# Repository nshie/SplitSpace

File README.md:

# SplitSpace
A regular 60% keyboard with the spacebar split into three buttons

### Motivation
Thumbs are our most dextrous digits, so why would we ever limit them to one button (let alone one SHARED button) on a keyboard? Every other finger is assigned numerous keys... This keyboard is a crude attempt to remedy that. It doesn't fix a lot of other issues with keyboards, but those are separate projects.

(My old keyboard PCB broke and I needed a replacement)

### Design
- fits in KBDFans 5 degree 60% case (the case I owned at the time of designing this PCB)
- hotswappable with MX style switches
- USB Type-C
- RGB underglow
- 3 spacebar keys
  - 2.25u, 1.25, and 2.75u (shift and modifier keys in ANSI layout keycaps)

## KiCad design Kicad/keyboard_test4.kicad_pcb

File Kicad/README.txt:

keyboard_test6 is the final production file

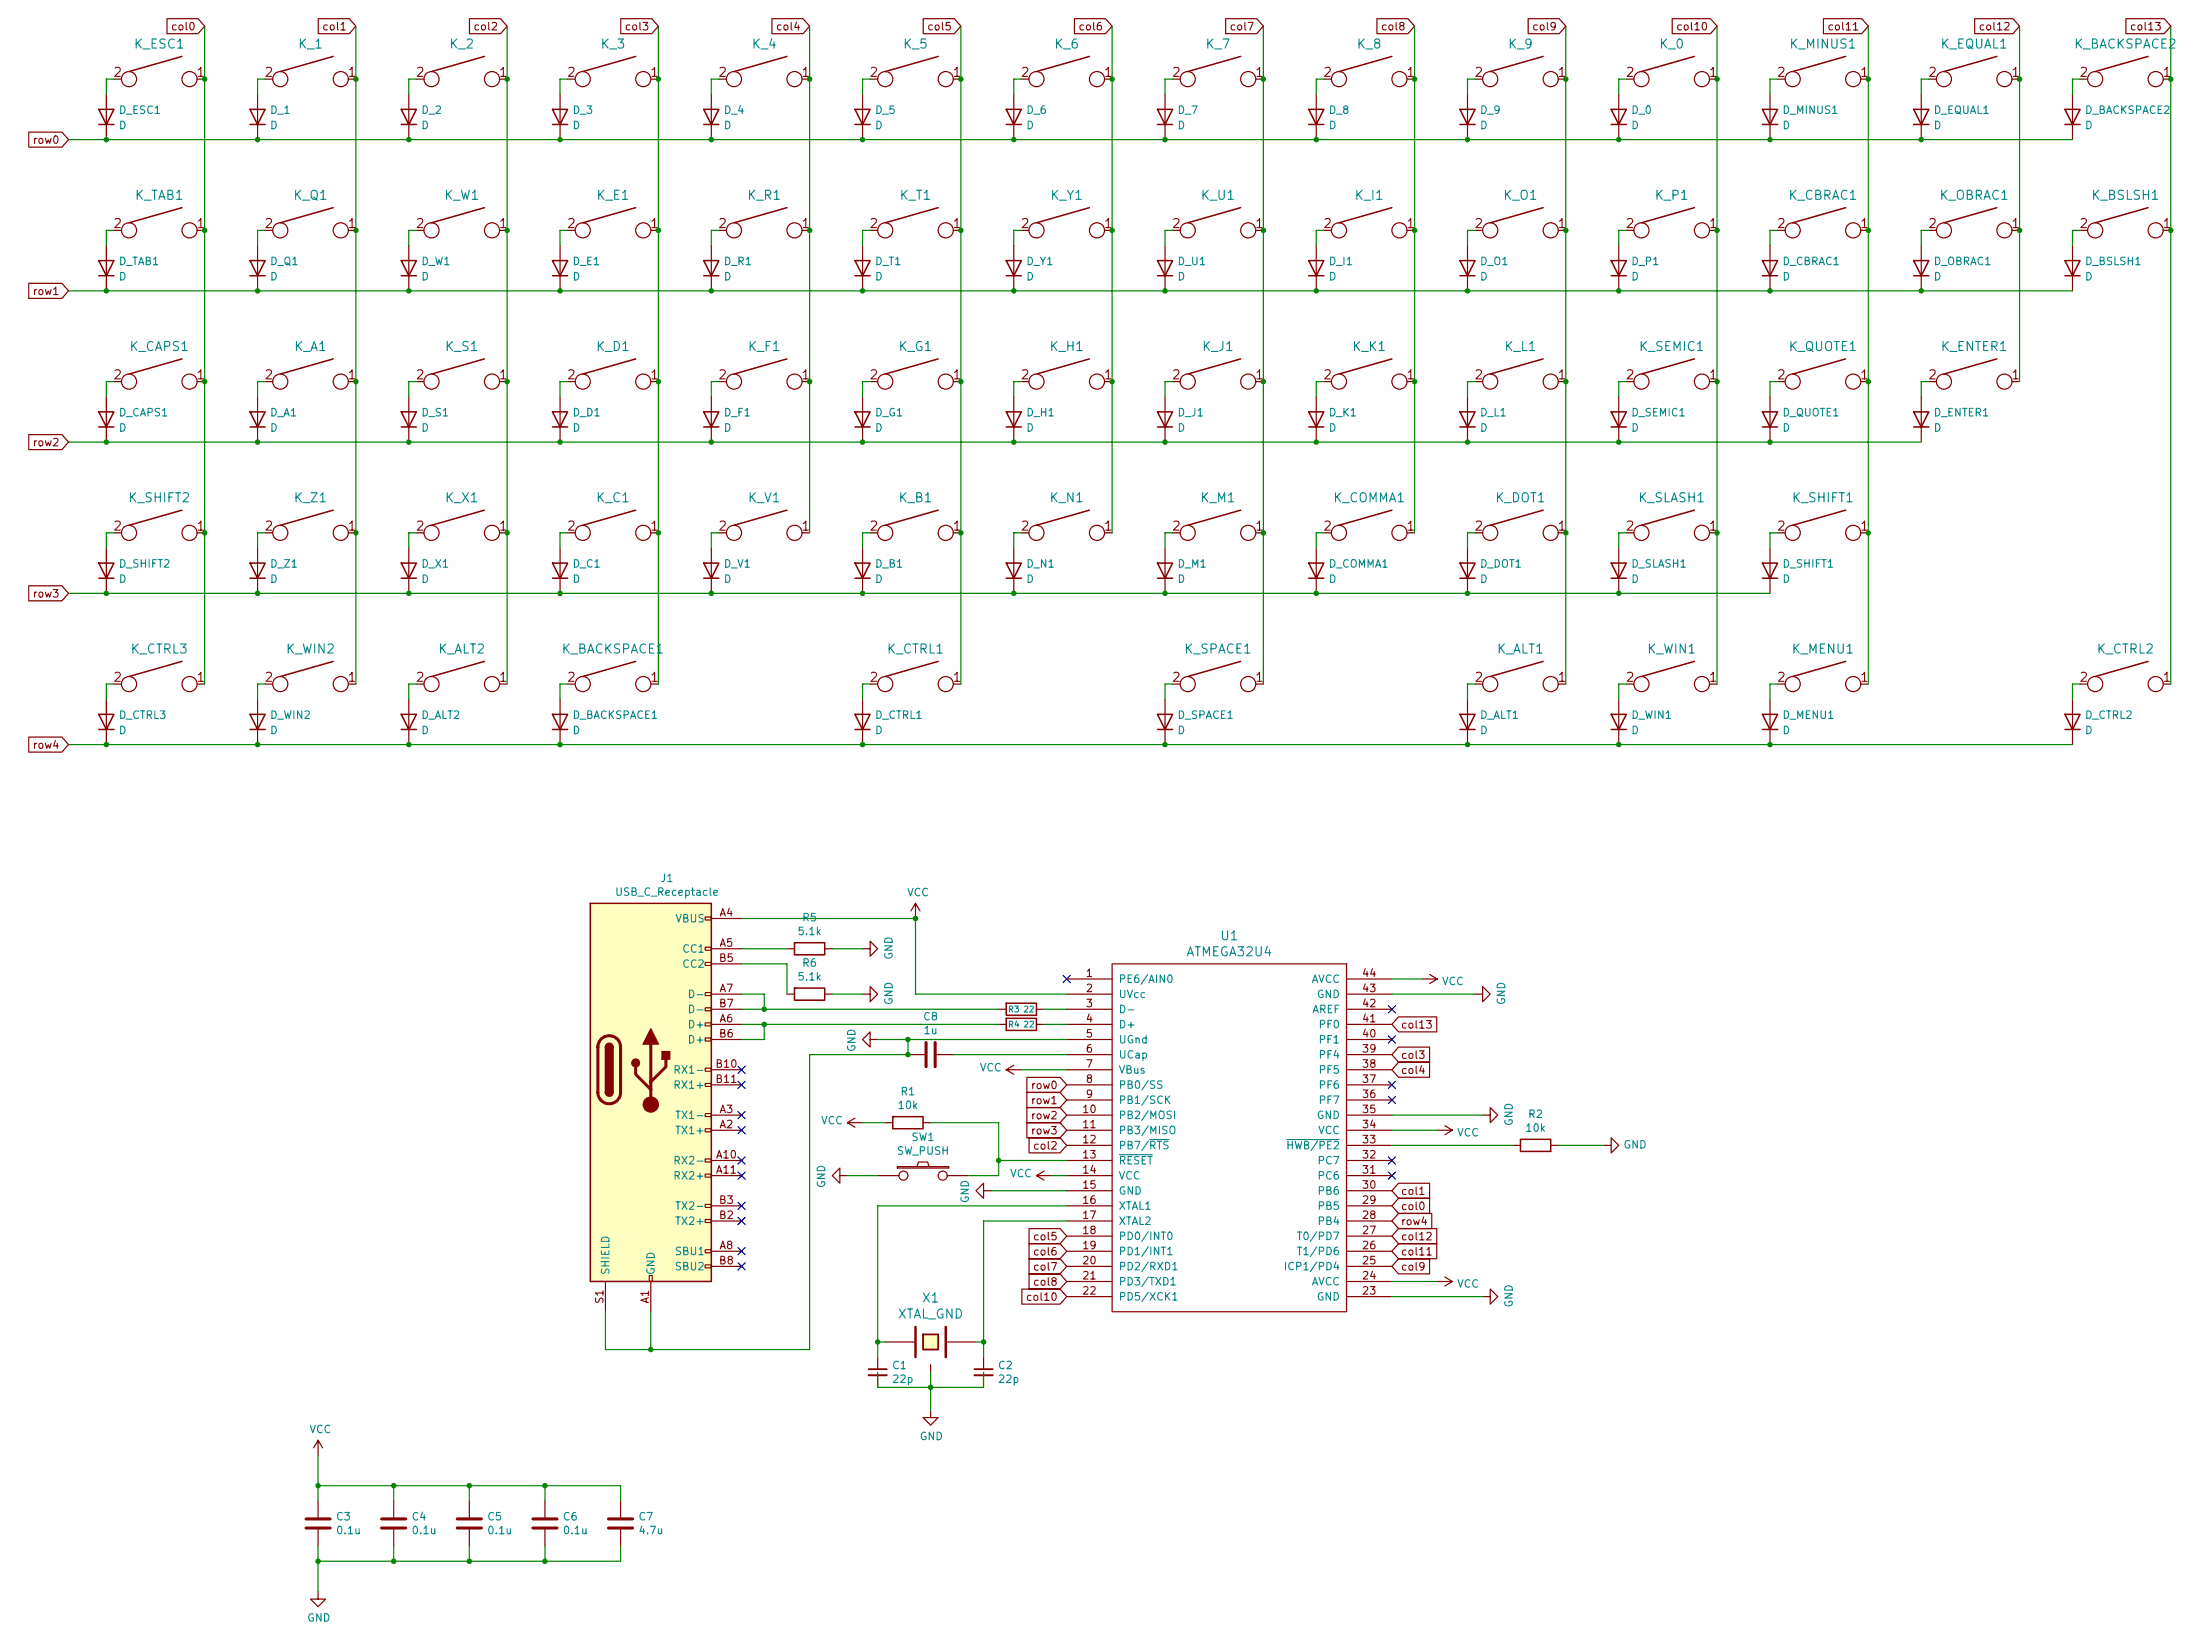
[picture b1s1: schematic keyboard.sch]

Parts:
C1, C2: 22p; C_0805_2012Metric_Pad1.15x1.40mm_HandSolder
C3, C4, C5, C6: 0.1u; C_0805_2012Metric_Pad1.15x1.40mm_HandSolder
C7: 4.7u; C_0805_2012Metric_Pad1.15x1.40mm_HandSolder
C8: 1u
D_0, D_1, D_2, D_3, D_4, D_5, D_6, D_7, D_8, D_9: D; D_SOD123_axial
D_A1: D; D_SOD123_axial
D_ALT1, D_ALT2: D; D_SOD123_axial
D_B1: D; D_SOD123_axial
D_BACKSPACE1, D_BACKSPACE2: D; D_SOD123_axial
D_BSLSH1: D; D_SOD123_axial
D_C1: D; D_SOD123_axial
D_CAPS1: D; D_SOD123_axial
D_CBRAC1: D; D_SOD123_axial
D_COMMA1: D; D_SOD123_axial
D_CTRL1, D_CTRL2, D_CTRL3: D; D_SOD123_axial
D_D1: D; D_SOD123_axial
D_DOT1: D; D_SOD123_axial
D_E1: D; D_SOD123_axial
D_ENTER1: D; D_SOD123_axial
D_EQUAL1: D; D_SOD123_axial
D_ESC1: D; D_SOD123_axial
D_F1: D; D_SOD123_axial
D_G1: D; D_SOD123_axial
D_H1: D; D_SOD123_axial
D_I1: D; D_SOD123_axial
D_J1: D; D_SOD123_axial
D_K1: D; D_SOD123_axial
D_L1: D; D_SOD123_axial
D_M1: D; D_SOD123_axial
D_MENU1: D; D_SOD123_axial
D_MINUS1: D; D_SOD123_axial
D_N1: D; D_SOD123_axial
D_O1: D; D_SOD123_axial
D_OBRAC1: D; D_SOD123_axial
D_P1: D; D_SOD123_axial
D_Q1: D; D_SOD123_axial
D_QUOTE1: D; D_SOD123_axial
D_R1: D; D_SOD123_axial
D_S1: D; D_SOD123_axial
D_SEMIC1: D; D_SOD123_axial
D_SHIFT1, D_SHIFT2: D; D_SOD123_axial
D_SLASH1: D; D_SOD123_axial
D_SPACE1: D; D_SOD123_axial
D_T1: D; D_SOD123_axial
D_TAB1: D; D_SOD123_axial
D_U1: D; D_SOD123_axial
D_V1: D; D_SOD123_axial
D_W1: D; D_SOD123_axial
D_WIN1, D_WIN2: D; D_SOD123_axial
D_X1: D; D_SOD123_axial
D_Y1: D; D_SOD123_axial
D_Z1: D; D_SOD123_axial
J1: USB_C_Receptacle
K_0, K_1, K_2, K_3, K_4, K_5, K_6, K_7, K_8, K_9: KEYSW; MXOnly-1U-Hotswap
K_A1: KEYSW; MXOnly-1U-Hotswap
K_ALT1, K_ALT2: KEYSW; MXOnly-1.25U-Hotswap
K_B1: KEYSW; MXOnly-1U-Hotswap
K_BACKSPACE1: KEYSW; MXOnly-2.25U-Hotswap
K_BACKSPACE2: KEYSW; MXOnly-2U-Hotswap-ReversedStabilizers
K_BSLSH1: KEYSW; MXOnly-1.5U-Hotswap
K_C1: KEYSW; MXOnly-1U-Hotswap
K_CAPS1: KEYSW; MXOnly-1.75U-Hotswap
K_CBRAC1: KEYSW; MXOnly-1U-Hotswap
K_COMMA1: KEYSW; MXOnly-1U-Hotswap
K_CTRL1, K_CTRL2, K_CTRL3: KEYSW; MXOnly-1.25U-Hotswap
K_D1: KEYSW; MXOnly-1U-Hotswap
K_DOT1: KEYSW; MXOnly-1U-Hotswap
K_E1: KEYSW; MXOnly-1U-Hotswap
K_ENTER1: KEYSW; MXOnly-2.25U-Hotswap-ReversedStabilizers
K_EQUAL1: KEYSW; MXOnly-1U-Hotswap
K_ESC1: KEYSW; MXOnly-1U-Hotswap
K_F1: KEYSW; MXOnly-1U-Hotswap
K_G1: KEYSW; MXOnly-1U-Hotswap
K_H1: KEYSW; MXOnly-1U-Hotswap
K_I1: KEYSW; MXOnly-1U-Hotswap
K_J1: KEYSW; MXOnly-1U-Hotswap
K_K1: KEYSW; MXOnly-1U-Hotswap
K_L1: KEYSW; MXOnly-1U-Hotswap
K_M1: KEYSW; MXOnly-1U-Hotswap
K_MENU1: KEYSW; MXOnly-1.25U-Hotswap
K_MINUS1: KEYSW; MXOnly-1U-Hotswap
K_N1: KEYSW; MXOnly-1U-Hotswap
K_O1: KEYSW; MXOnly-1U-Hotswap
K_OBRAC1: KEYSW; MXOnly-1U-Hotswap
K_P1: KEYSW; MXOnly-1U-Hotswap
K_Q1: KEYSW; MXOnly-1U-Hotswap
K_QUOTE1: KEYSW; MXOnly-1U-Hotswap
K_R1: KEYSW; MXOnly-1U-Hotswap
K_S1: KEYSW; MXOnly-1U-Hotswap
K_SEMIC1: KEYSW; MXOnly-1U-Hotswap
K_SHIFT1: KEYSW; MXOnly-2.75U-Hotswap-ReversedStabilizers
K_SHIFT2: KEYSW; MXOnly-2.25U-Hotswap-ReversedStabilizers
K_SLASH1: KEYSW; MXOnly-1U-Hotswap
K_SPACE1: KEYSW; MXOnly-2.75U-Hotswap
K_T1: KEYSW; MXOnly-1U-Hotswap
K_TAB1: KEYSW; MXOnly-1.5U-Hotswap
K_U1: KEYSW; MXOnly-1U-Hotswap
K_V1: KEYSW; MXOnly-1U-Hotswap
K_W1: KEYSW; MXOnly-1U-Hotswap
K_WIN1, K_WIN2: KEYSW; MXOnly-1.25U-Hotswap
K_X1: KEYSW; MXOnly-1U-Hotswap
K_Y1: KEYSW; MXOnly-1U-Hotswap
K_Z1: KEYSW; MXOnly-1U-Hotswap
R1: 10k; R_0805_2012Metric_Pad1.15x1.40mm_HandSolder
R2: 10k
R3, R4: 22; R_0805_2012Metric_Pad1.15x1.40mm_HandSolder
R5, R6: 5.1k; R_0805_2012Metric_Pad1.15x1.40mm_HandSolder
SW1: SW_PUSH; SW_SPST_TL3342
U1: ATMEGA32U4; ATmega32U4
X1: XTAL_GND; FA-238

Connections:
GND: C1.2, C2.2, C3.2, C4.2, C5.2, C6.2, C7.2, C8.1, J1.A1 (GND), J1.A12 (GND), J1.B1 (GND), J1.B12 (GND), J1.S1 (SHIELD), R2.2, R5.1, R6.1, SW1.1, U1.5 (UGnd), U1.15 (GND), U1.23 (GND), U1.35 (GND), U1.43 (GND), X1.3
unnamed: C1.1, U1.16 (XTAL1), X1.1
unnamed: C2.1, U1.17 (XTAL2), X1.2
unnamed: C8.2, U1.6 (UCap)
unnamed: D_0.2 (A), K_0.2
unnamed: D_1.2 (A), K_1.2
unnamed: D_2.2 (A), K_2.2
unnamed: D_3.2 (A), K_3.2
unnamed: D_4.2 (A), K_4.2
unnamed: D_5.2 (A), K_5.2
unnamed: D_6.2 (A), K_6.2
unnamed: D_7.2 (A), K_7.2
unnamed: D_8.2 (A), K_8.2
unnamed: D_9.2 (A), K_9.2
unnamed: D_A1.2 (A), K_A1.2
unnamed: D_ALT1.2 (A), K_ALT1.2
unnamed: D_ALT2.2 (A), K_ALT2.2
unnamed: D_B1.2 (A), K_B1.2
unnamed: D_BACKSPACE1.2 (A), K_BACKSPACE1.2
unnamed: D_BACKSPACE2.2 (A), K_BACKSPACE2.2
unnamed: D_BSLSH1.2 (A), K_BSLSH1.2
unnamed: D_C1.2 (A), K_C1.2
unnamed: D_CAPS1.2 (A), K_CAPS1.2
unnamed: D_CBRAC1.2 (A), K_CBRAC1.2
unnamed: D_COMMA1.2 (A), K_COMMA1.2
unnamed: D_CTRL1.2 (A), K_CTRL1.2
unnamed: D_CTRL2.2 (A), K_CTRL2.2
unnamed: D_CTRL3.2 (A), K_CTRL3.2
unnamed: D_D1.2 (A), K_D1.2
unnamed: D_DOT1.2 (A), K_DOT1.2
unnamed: D_E1.2 (A), K_E1.2
unnamed: D_ENTER1.2 (A), K_ENTER1.2
unnamed: D_EQUAL1.2 (A), K_EQUAL1.2
unnamed: D_ESC1.2 (A), K_ESC1.2
unnamed: D_F1.2 (A), K_F1.2
unnamed: D_G1.2 (A), K_G1.2
unnamed: D_H1.2 (A), K_H1.2
unnamed: D_I1.2 (A), K_I1.2
unnamed: D_J1.2 (A), K_J1.2
unnamed: D_K1.2 (A), K_K1.2
unnamed: D_L1.2 (A), K_L1.2
unnamed: D_M1.2 (A), K_M1.2
unnamed: D_MENU1.2 (A), K_MENU1.2
unnamed: D_MINUS1.2 (A), K_MINUS1.2
unnamed: D_N1.2 (A), K_N1.2
unnamed: D_O1.2 (A), K_O1.2
unnamed: D_OBRAC1.2 (A), K_OBRAC1.2
unnamed: D_P1.2 (A), K_P1.2
unnamed: D_Q1.2 (A), K_Q1.2
unnamed: D_QUOTE1.2 (A), K_QUOTE1.2
unnamed: D_R1.2 (A), K_R1.2
unnamed: D_S1.2 (A), K_S1.2
unnamed: D_SEMIC1.2 (A), K_SEMIC1.2
unnamed: D_SHIFT1.2 (A), K_SHIFT1.2
unnamed: D_SHIFT2.2 (A), K_SHIFT2.2
unnamed: D_SLASH1.2 (A), K_SLASH1.2
unnamed: D_SPACE1.2 (A), K_SPACE1.2
unnamed: D_T1.2 (A), K_T1.2
unnamed: D_TAB1.2 (A), K_TAB1.2
unnamed: D_U1.2 (A), K_U1.2
unnamed: D_V1.2 (A), K_V1.2
unnamed: D_W1.2 (A), K_W1.2
unnamed: D_WIN1.2 (A), K_WIN1.2
unnamed: D_WIN2.2 (A), K_WIN2.2
unnamed: D_X1.2 (A), K_X1.2
unnamed: D_Y1.2 (A), K_Y1.2
unnamed: D_Z1.2 (A), K_Z1.2
unnamed: J1.A5 (CC1), R5.2
unnamed: J1.A6 (D+), J1.B6 (D+), R4.2
unnamed: J1.A7 (D-), J1.B7 (D-), R3.2
unnamed: J1.B5 (CC2), R6.2
unnamed: R1.1, SW1.2, U1.13 (~RESET)
unnamed: R2.1, U1.33 (~HWB/PE2)
unnamed: R3.1, U1.3 (D-)
unnamed: R4.1, U1.4 (D+)
VCC: C3.1, C4.1, C5.1, C6.1, C7.1, J1.A4 (VBUS), J1.A9 (VBUS), J1.B4 (VBUS), J1.B9 (VBUS), R1.2, U1.2 (UVcc), U1.7 (VBus), U1.14 (VCC), U1.24 (AVCC), U1.34 (VCC), U1.44 (AVCC)
col0: K_CAPS1.1, K_CTRL3.1, K_ESC1.1, K_SHIFT2.1, K_TAB1.1, U1.29 (PB5)
col1: K_1.1, K_A1.1, K_Q1.1, K_WIN2.1, K_Z1.1, U1.30 (PB6)
col2: K_2.1, K_ALT2.1, K_S1.1, K_W1.1, K_X1.1, U1.12 (PB7/~RTS)
col3: K_3.1, K_BACKSPACE1.1, K_C1.1, K_D1.1, K_E1.1, U1.39 (PF4)
col4: K_4.1, K_F1.1, K_R1.1, K_V1.1, U1.38 (PF5)
col5: K_5.1, K_B1.1, K_CTRL1.1, K_G1.1, K_T1.1, U1.18 (PD0/INT0)
col6: K_6.1, K_H1.1, K_N1.1, K_Y1.1, U1.19 (PD1/INT1)
col7: K_7.1, K_J1.1, K_M1.1, K_SPACE1.1, K_U1.1, U1.20 (PD2/RXD1)
col8: K_8.1, K_COMMA1.1, K_I1.1, K_K1.1, U1.21 (PD3/TXD1)
col9: K_9.1, K_ALT1.1, K_DOT1.1, K_L1.1, K_O1.1, U1.25 (ICP1/PD4)
col10: K_0.1, K_P1.1, K_SEMIC1.1, K_SLASH1.1, K_WIN1.1, U1.22 (PD5/XCK1)
col11: K_CBRAC1.1, K_MENU1.1, K_MINUS1.1, K_QUOTE1.1, K_SHIFT1.1, U1.26 (T1/PD6)
col12: K_ENTER1.1, K_EQUAL1.1, K_OBRAC1.1, U1.27 (T0/PD7)
col13: K_BACKSPACE2.1, K_BSLSH1.1, K_CTRL2.1, U1.41 (PF0)
row0: D_0.1 (K), D_1.1 (K), D_2.1 (K), D_3.1 (K), D_4.1 (K), D_5.1 (K), D_6.1 (K), D_7.1 (K), D_8.1 (K), D_9.1 (K), D_BACKSPACE2.1 (K), D_EQUAL1.1 (K), D_ESC1.1 (K), D_MINUS1.1 (K), U1.8 (PB0/SS)
row1: D_BSLSH1.1 (K), D_CBRAC1.1 (K), D_E1.1 (K), D_I1.1 (K), D_O1.1 (K), D_OBRAC1.1 (K), D_P1.1 (K), D_Q1.1 (K), D_R1.1 (K), D_T1.1 (K), D_TAB1.1 (K), D_U1.1 (K), D_W1.1 (K), D_Y1.1 (K), U1.9 (PB1/SCK)
row2: D_A1.1 (K), D_CAPS1.1 (K), D_D1.1 (K), D_ENTER1.1 (K), D_F1.1 (K), D_G1.1 (K), D_H1.1 (K), D_J1.1 (K), D_K1.1 (K), D_L1.1 (K), D_QUOTE1.1 (K), D_S1.1 (K), D_SEMIC1.1 (K), U1.10 (PB2/MOSI)
row3: D_B1.1 (K), D_C1.1 (K), D_COMMA1.1 (K), D_DOT1.1 (K), D_M1.1 (K), D_N1.1 (K), D_SHIFT1.1 (K), D_SHIFT2.1 (K), D_SLASH1.1 (K), D_V1.1 (K), D_X1.1 (K), D_Z1.1 (K), U1.11 (PB3/MISO)
row4: D_ALT1.1 (K), D_ALT2.1 (K), D_BACKSPACE1.1 (K), D_CTRL1.1 (K), D_CTRL2.1 (K), D_CTRL3.1 (K), D_MENU1.1 (K), D_SPACE1.1 (K), D_WIN1.1 (K), D_WIN2.1 (K), U1.28 (PB4)

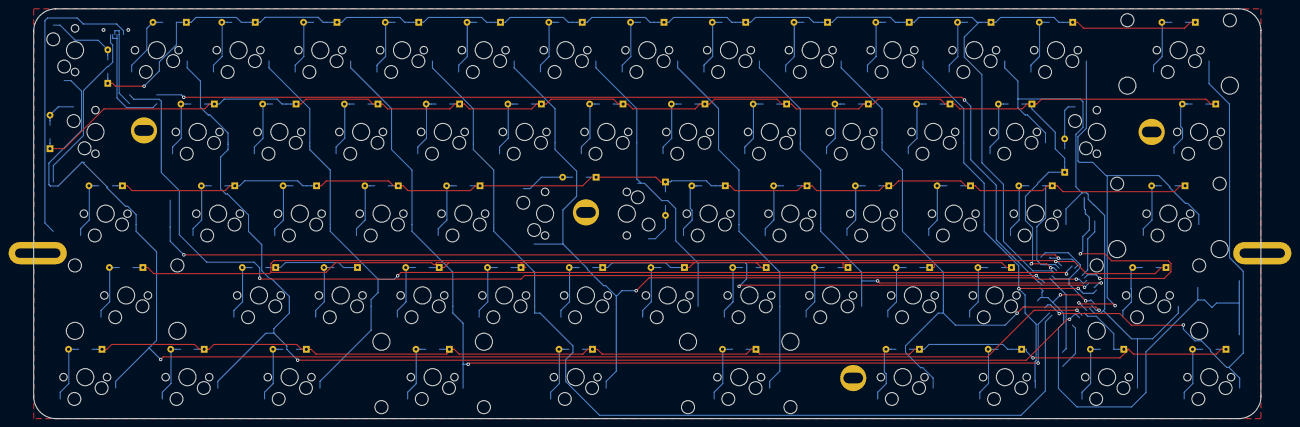
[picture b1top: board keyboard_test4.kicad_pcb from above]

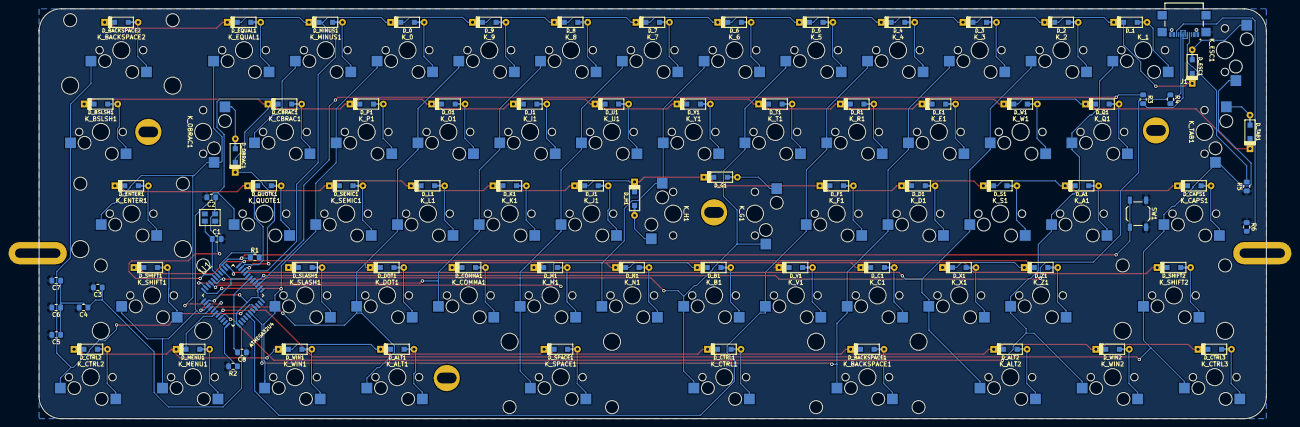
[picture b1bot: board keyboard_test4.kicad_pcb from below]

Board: 2 copper layers, 286.0 x 95.5 mm, 150 parts (81 on the bottom side), 95 nets.

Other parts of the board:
Poker_oval_hole1, Poker_oval_hole2, Poker_oval_hole3, Poker_oval_hole4: VAL**; Poker_oval_hole
Poker_side_edge_long1, Poker_side_edge_long2: VAL**; Poker_side_edge_long

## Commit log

2023-10-05 Kicad and QMK files
2023-10-06 Added Images
2023-10-06 JPG of top-down
2023-10-15 fixed capitalization
